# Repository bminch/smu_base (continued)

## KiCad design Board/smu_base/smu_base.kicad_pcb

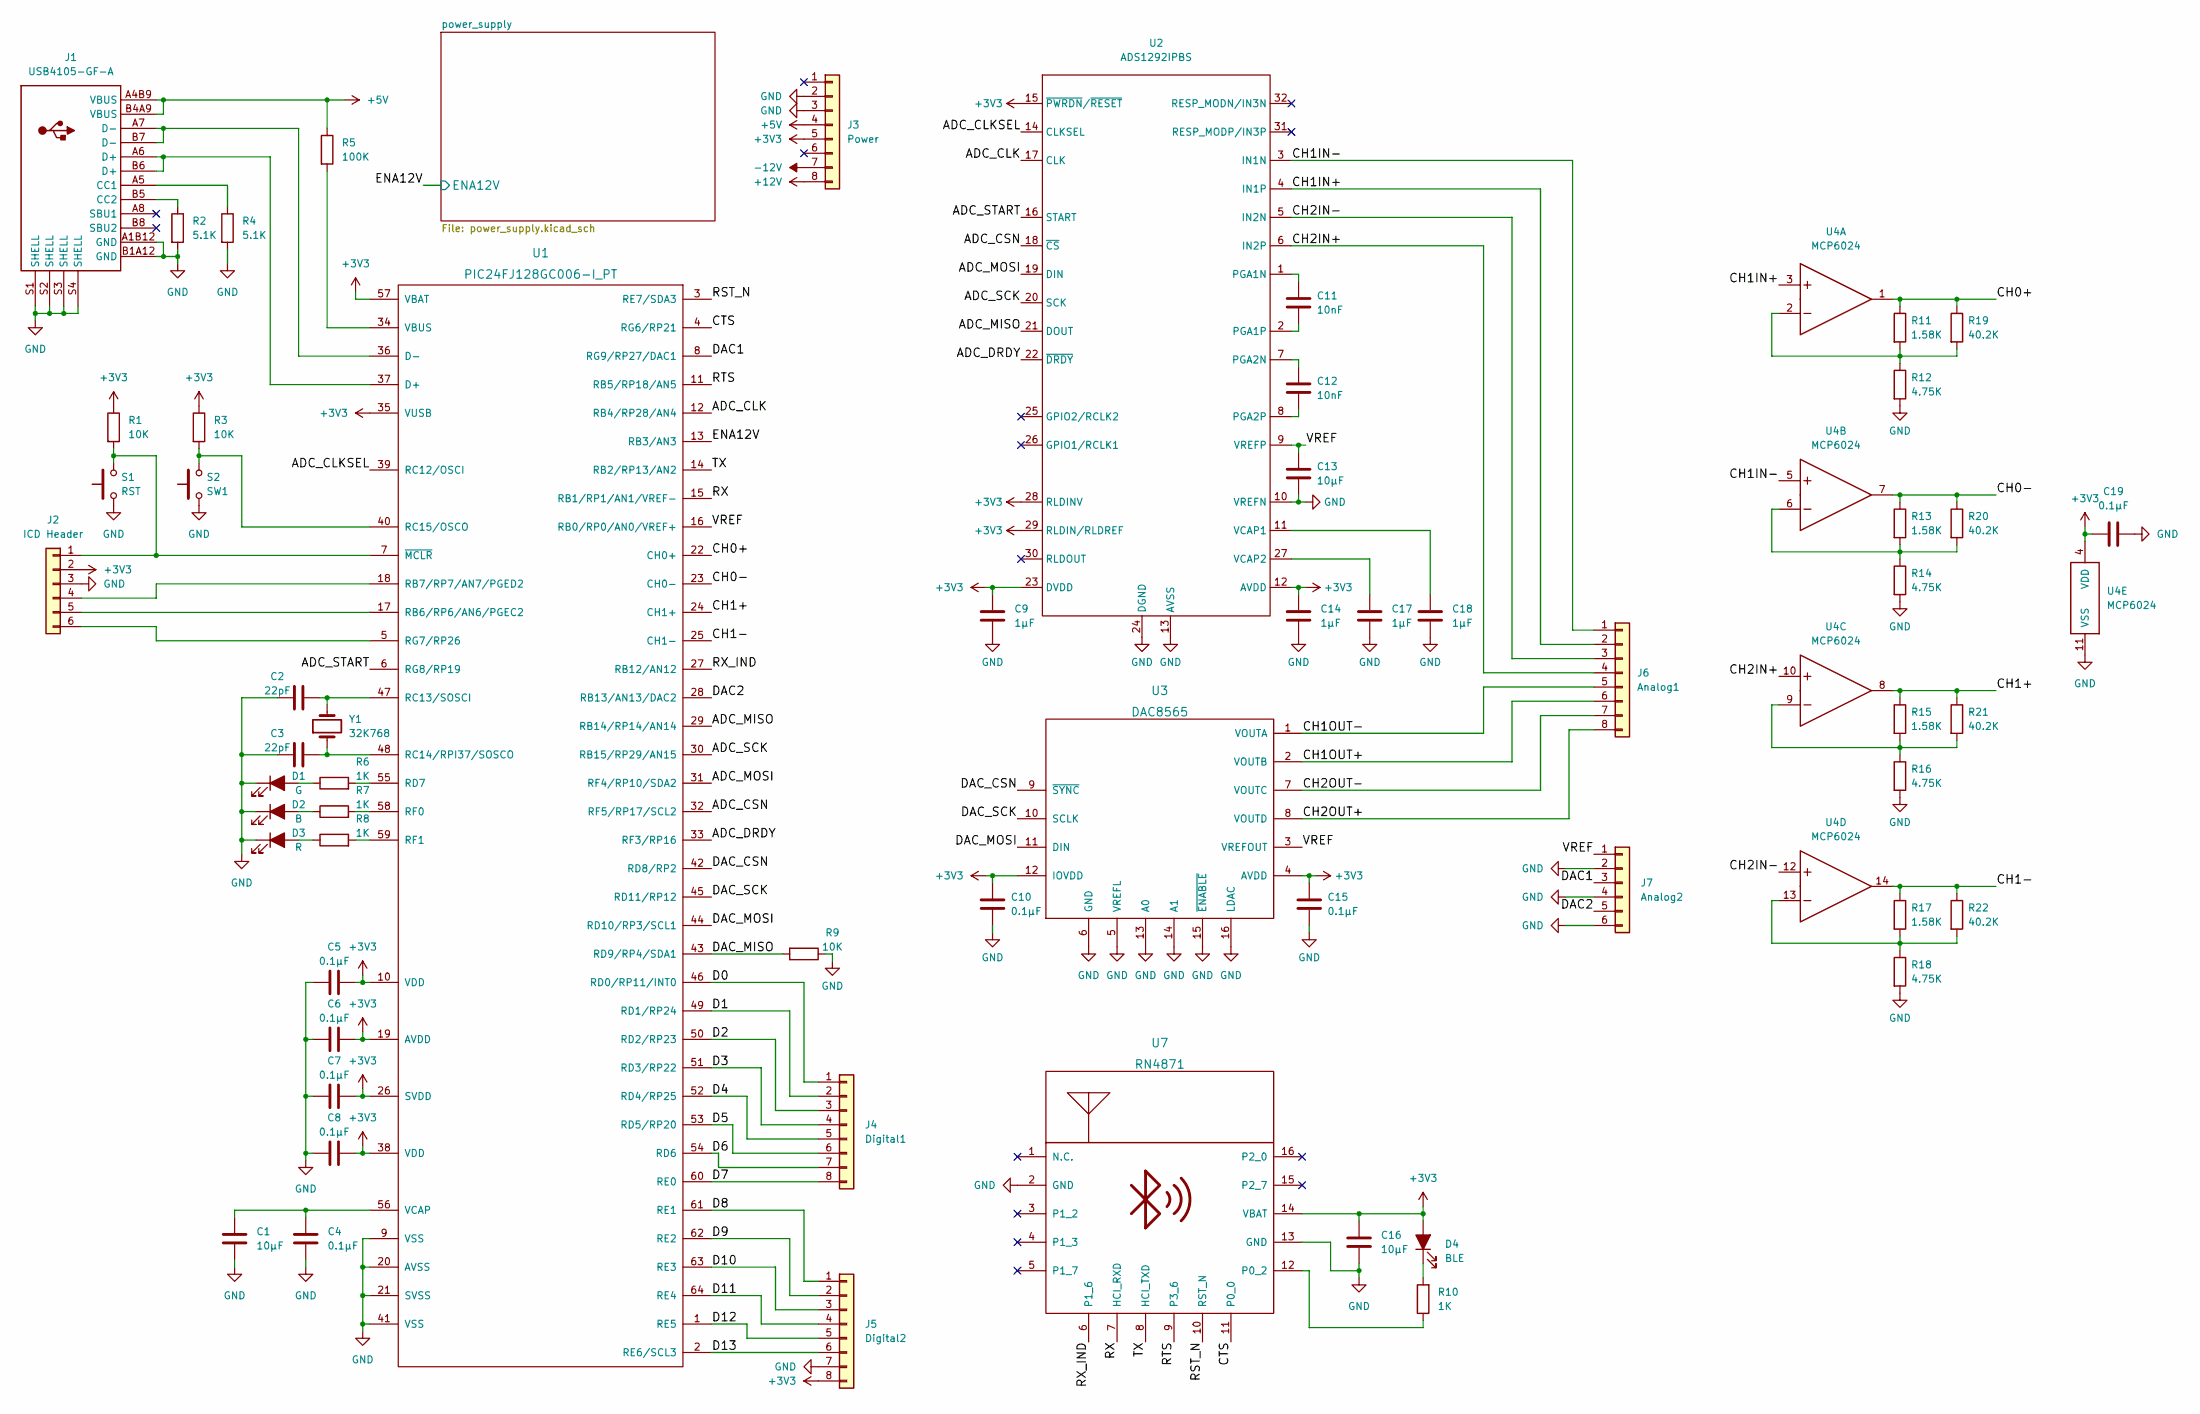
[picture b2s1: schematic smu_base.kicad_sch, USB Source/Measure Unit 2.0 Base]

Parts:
C1, C13, C16: 10µF; C_0603_1608Metric
C2, C3: 22pF; C_0603_1608Metric
C4, C5, C6, C7, C8, C10, C15, C19: 0.1µF; C_0603_1608Metric
C9, C14, C17, C18: 1µF; C_0603_1608Metric
C11, C12: 10nF; C_0603_1608Metric
D1: G; LED_0805_2012Metric
D2: B; LED_0805_2012Metric
D3: R; LED_0805_2012Metric
D4: BLE; LED_0805_2012Metric
J1: USB4105-GF-A
J2: ICD Header; ICD3_header
J3: Power; PinSocket_1x08_P2.54mm_Vertical
J4: Digital1; PinSocket_1x08_P2.54mm_Vertical
J5: Digital2; PinSocket_1x08_P2.54mm_Vertical
J6: Analog1; PinSocket_1x08_P2.54mm_Vertical
J7: Analog2; PinSocket_1x06_P2.54mm_Vertical
R1, R3, R9: 10K; R_0603_1608Metric
R2, R4: 5.1K; R_0603_1608Metric
R5: 100K; R_0603_1608Metric
R6, R7, R8, R10: 1K; R_0603_1608Metric
R11, R13, R15, R17: 1.58K; R_0603_1608Metric
R12, R14, R16, R18: 4.75K; R_0603_1608Metric
R19, R20, R21, R22: 40.2K; R_0603_1608Metric
S1: RST; TL3301NFxxxxJ
S2: SW1; TL3301AFxxxxJ
U1: PIC24FJ128GC006-I_PT; TQFP-64_10x10mm_P0.5mm
U2: ADS1292IPBS; PQFP-32_5x5mm_P0.5mm
U3: DAC8565; TSSOP-16_4.4x5mm_P0.65mm
U4: MCP6024; TSSOP-14_4.4x5mm_P0.65mm
U7: RN4871
Y1: 32K768; Crystal_SMD_2012-2Pin_2.0x1.2mm

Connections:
+3V3: C5.2, C6.2, C7.2, C8.2, C9.1, C10.1, C14.1, C15.1, C16.1, C19.1, D4.2 (A), J2.2, J3.5, J5.8, R1.1, R3.1, U1.10 (VDD), U1.19 (AVDD), U1.26 (SVDD), U1.35 (VUSB), U1.38 (VDD), U1.57 (VBAT), U2.12 (AVDD), U2.15 (~PWRDN/~RESET), U2.23 (DVDD), U2.28 (RLDINV), U2.29 (RLDIN/RLDREF), U3.4 (AVDD), U3.12 (IOVDD), U4.4 (VDD), U7.14 (VBAT); also elsewhere on the board
+5V: J1.A4B9 (VBUS), J1.B4A9 (VBUS), J3.4, R5.1; also elsewhere on the board
+12V: J3.8; also elsewhere on the board
-12V: J3.7; also elsewhere on the board
/ADC_CLK: U1.12 (RB4/RP28/AN4), U2.17 (CLK)
/ADC_CLKSEL: U1.39 (RC12/OSCI), U2.14 (CLKSEL)
/ADC_CSN: U1.32 (RF5/RP17/SCL2), U2.18 (~CS)
/ADC_DRDY: U1.33 (RF3/RP16), U2.22 (~DRDY)
/ADC_MISO: U1.29 (RB14/RP14/AN14), U2.21 (DOUT)
/ADC_MOSI: U1.31 (RF4/RP10/SDA2), U2.19 (DIN)
/ADC_SCK: U1.30 (RB15/RP29/AN15), U2.20 (SCK)
/ADC_START: U1.6 (RG8/RP19), U2.16 (START)
/CH0+: R11.1, R19.1, U1.22 (CH0+), U4.1
/CH0-: R13.1, R20.1, U1.23 (CH0-), U4.7
/CH1+: R15.1, R21.1, U1.24 (CH1+), U4.8
/CH1-: R17.1, R22.1, U1.25 (CH1-), U4.14
/CH1IN+: J6.2, U2.4 (IN1P), U4.3
/CH1IN-: J6.1, U2.3 (IN1N), U4.5
/CH1OUT+: J6.6, U3.2 (VOUTB)
/CH1OUT-: J6.5, U3.1 (VOUTA)
/CH2IN+: J6.4, U2.6 (IN2P), U4.10
/CH2IN-: J6.3, U2.5 (IN2N), U4.12
/CH2OUT+: J6.8, U3.8 (VOUTD)
/CH2OUT-: J6.7, U3.7 (VOUTC)
/CTS: U1.4 (RG6/RP21), U7.11 (P0_0)
/D0: J4.1, U1.46 (RD0/RP11/INT0)
/D1: J4.2, U1.49 (RD1/RP24)
/D2: J4.3, U1.50 (RD2/RP23)
/D3: J4.4, U1.51 (RD3/RP22)
/D4: J4.5, U1.52 (RD4/RP25)
/D5: J4.6, U1.53 (RD5/RP20)
/D6: J4.7, U1.54 (RD6)
/D7: J4.8, U1.60 (RE0)
/D8: J5.1, U1.61 (RE1)
/D9: J5.2, U1.62 (RE2)
/D10: J5.3, U1.63 (RE3)
/D11: J5.4, U1.64 (RE4)
/D12: J5.5, U1.1 (RE5)
/D13: J5.6, U1.2 (RE6/SCL3)
/DAC1: J7.3, U1.8 (RG9/RP27/DAC1)
/DAC2: J7.5, U1.28 (RB13/AN13/DAC2)
/DAC_CSN: U1.42 (RD8/RP2), U3.9 (~SYNC)
/DAC_MISO: R9.2, U1.43 (RD9/RP4/SDA1)
/DAC_MOSI: U1.44 (RD10/RP3/SCL1), U3.11 (DIN)
/DAC_SCK: U1.45 (RD11/RP12), U3.10 (SCLK)
/ENA12V: U1.13 (RB3/AN3); also elsewhere on the board
/RST_N: U1.3 (RE7/SDA3), U7.10 (RST_N)
/RTS: U1.11 (RB5/RP18/AN5), U7.9 (P3_6)
/RX: U1.15 (RB1/RP1/AN1/VREF-), U7.7 (HCI_RXD)
/RX_IND: U1.27 (RB12/AN12), U7.6 (P1_6)
/TX: U1.14 (RB2/RP13/AN2), U7.8 (HCI_TXD)
/VREF: C13.1, J7.1, U1.16 (RB0/RP0/AN0/VREF+), U2.9 (VREFP), U3.3 (VREFOUT)
GND: C1.2, C2.1, C3.1, C4.2, C5.1, C6.1, C7.1, C8.1, C9.2, C10.2, C13.2, C14.2, C15.2, C16.2, C17.2, C18.2, C19.2, D1.1 (K), D2.1 (K), D3.1 (K), J1.A1B12 (GND), J1.B1A12 (GND), J1.S1 (SHELL), J1.S2 (SHELL), J1.S3 (SHELL), J1.S4 (SHELL), J2.3, J3.2, J3.3, J5.7, J7.2, J7.4, J7.6, R2.2, R4.2, R9.1, R12.2, R14.2, R16.2, R18.2, S1.1, S2.1, U1.9 (VSS), U1.20 (AVSS), U1.21 (SVSS), U1.41 (VSS), U2.10 (VREFN), U2.13 (AVSS), U2.24 (DGND), U3.5 (VREFL), U3.6 (GND), U3.13 (A0), U3.14 (A1), U3.15 (~ENABLE), U3.16 (LDAC), U4.11 (VSS), U7.2 (GND), U7.13 (GND); also elsewhere on the board
unnamed: C1.1, C4.1, U1.56 (VCAP)
unnamed: C2.2, U1.47 (RC13/SOSCI), Y1.2
unnamed: C3.2, U1.48 (RC14/RPI37/SOSCO), Y1.1
unnamed: C11.1, U2.1 (PGA1N)
unnamed: C11.2, U2.2 (PGA1P)
unnamed: C12.1, U2.7 (PGA2N)
unnamed: C12.2, U2.8 (PGA2P)
unnamed: C17.1, U2.27 (VCAP2)
unnamed: C18.1, U2.11 (VCAP1)
unnamed: D1.2 (A), R6.1
unnamed: D2.2 (A), R7.1
unnamed: D3.2 (A), R8.1
unnamed: D4.1 (K), R10.2
unnamed: J1.A5 (CC1), R4.1
unnamed: J1.A6 (D+), J1.B6 (D+), U1.37 (D+)
unnamed: J1.A7 (D-), J1.B7 (D-), U1.36 (D-)
unnamed: J1.B5 (CC2), R2.1
unnamed: J2.1, R1.2, S1.2, U1.7 (~MCLR)
unnamed: J2.4, U1.18 (RB7/RP7/AN7/PGED2)
unnamed: J2.5, U1.17 (RB6/RP6/AN6/PGEC2)
unnamed: J2.6, U1.5 (RG7/RP26)
unnamed: R3.2, S2.2, U1.40 (RC15/OSCO)
unnamed: R5.2, U1.34 (VBUS)
unnamed: R6.2, U1.55 (RD7)
unnamed: R7.2, U1.58 (RF0)
unnamed: R8.2, U1.59 (RF1)
unnamed: R10.1, U7.12 (P0_2)
unnamed: R11.2, R12.1, R19.2, U4.2
unnamed: R13.2, R14.1, R20.2, U4.6
unnamed: R15.2, R16.1, R21.2, U4.9
unnamed: R17.2, R18.1, R22.2, U4.13

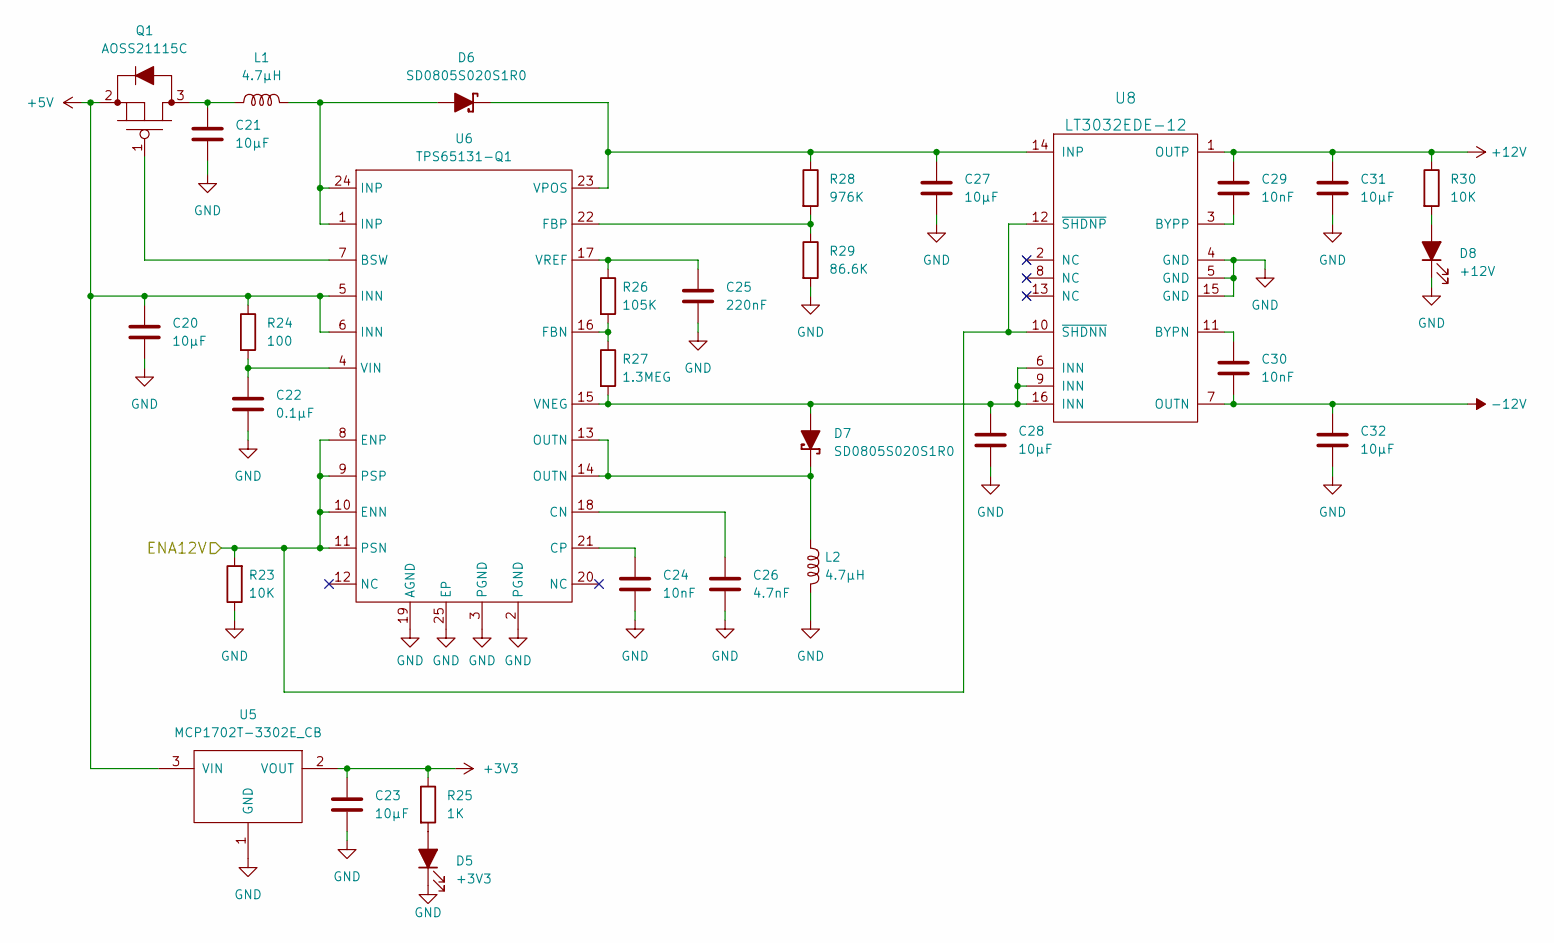
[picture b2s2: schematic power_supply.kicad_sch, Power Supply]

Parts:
C20, C21, C23, C27, C28, C31, C32: 10µF; C_0603_1608Metric
C22: 0.1µF; C_0603_1608Metric
C24, C29, C30: 10nF; C_0603_1608Metric
C25: 220nF; C_0603_1608Metric
C26: 4.7nF; C_0603_1608Metric
D5: +3V3; LED_0805_2012Metric
D6, D7: SD0805S020S1R0; D_0805_2012Metric
D8: +12V; LED_0805_2012Metric
L1, L2: 4.7µH; PA5003.182NLT
Q1: AOSS21115C; SOT-23
R23, R30: 10K; R_0603_1608Metric
R24: 100; R_0603_1608Metric
R25: 1K; R_0603_1608Metric
R26: 105K; R_0603_1608Metric
R27: 1.3MEG; R_0603_1608Metric
R28: 976K; R_0603_1608Metric
R29: 86.6K; R_0603_1608Metric
U5: MCP1702T-3302E_CB; SOT-23
U6: TPS65131-Q1; TPS65131-Q
U8: LT3032EDE-12; LT3032

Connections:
+3V3: C23.1, R25.1, U5.2 (VOUT); also elsewhere on the board
+5V: C20.1, Q1.2, R24.1, U5.3 (VIN), U6.5 (INN), U6.6 (INN); also elsewhere on the board
+12V: C29.1, C31.1, R30.1, U8.1 (OUTP); also elsewhere on the board
-12V: C30.2, C32.1, U8.7 (OUTN); also elsewhere on the board
/ENA12V: R23.2, U6.8 (ENP), U6.9 (PSP), U6.10 (ENN), U6.11 (PSN), U8.10 (~SHDNN), U8.12 (~SHDNP); also elsewhere on the board
GND: C20.2, C21.2, C22.2, C23.2, C24.2, C25.2, C26.2, C27.2, C28.2, C31.2, C32.2, D5.1 (K), D8.1 (K), L2.2, R23.1, R29.2, U5.1 (GND), U6.2 (PGND), U6.3 (PGND), U6.19 (AGND), U6.25 (EP), U8.4 (GND), U8.5 (GND), U8.15 (GND); also elsewhere on the board
unnamed: C21.1, L1.1, Q1.3
unnamed: C22.1, R24.2, U6.4 (VIN)
unnamed: C24.1, U6.21 (CP)
unnamed: C25.1, R26.1, U6.17 (VREF)
unnamed: C26.1, U6.18 (CN)
unnamed: C27.1, D6.1, R28.1, U6.23 (VPOS), U8.14 (INP)
unnamed: C28.1, D7.2, R27.2, U6.15 (VNEG), U8.6 (INN), U8.9 (INN), U8.16 (INN)
unnamed: C29.2, U8.3 (BYPP)
unnamed: C30.1, U8.11 (BYPN)
unnamed: D5.2 (A), R25.2
unnamed: D6.2, L1.2, U6.1 (INP), U6.24 (INP)
unnamed: D7.1, L2.1, U6.13 (OUTN), U6.14 (OUTN)
unnamed: D8.2 (A), R30.2
unnamed: Q1.1, U6.7 (BSW)
unnamed: R26.2, R27.1, U6.16 (FBN)
unnamed: R28.2, R29.1, U6.22 (FBP)

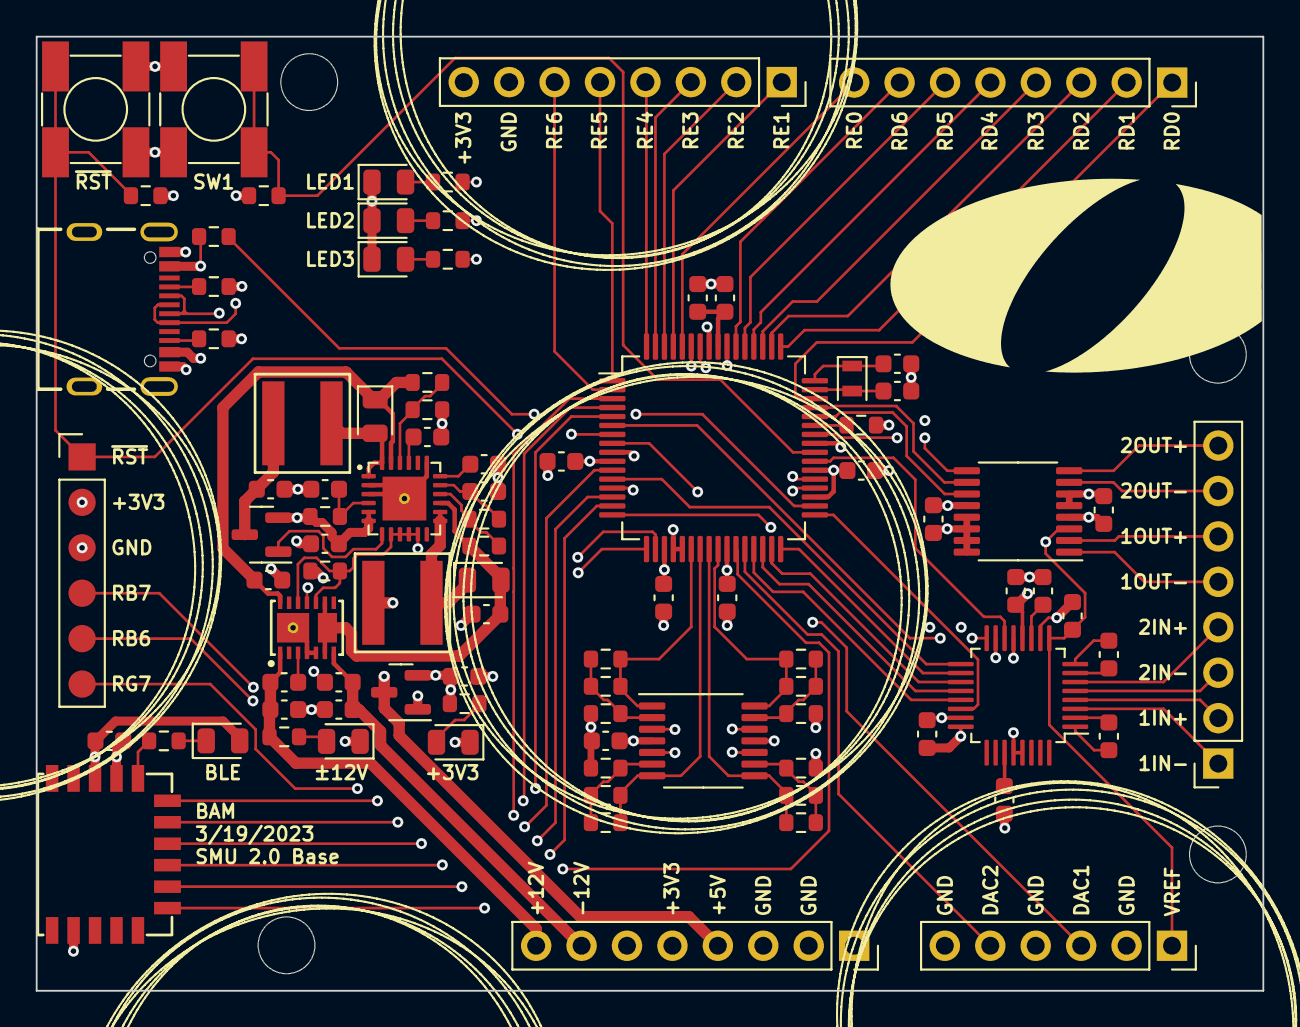
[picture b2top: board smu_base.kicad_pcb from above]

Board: 4 copper layers, 68.6 x 53.3 mm, 98 parts (1 on the bottom side), 100 nets.

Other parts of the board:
svg2mod, svg2mod#2, svg2mod#3, svg2mod#4, svg2mod#6: G***; gesture_ellipse
svg2mod#5: G***; OlinLogoTruncated_0.4in
svg2mod#7: G***; OlinLogoTruncatedLg

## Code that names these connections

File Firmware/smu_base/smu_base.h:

#ifndef _SMUBASE_H_
#define _SMUBASE_H_

#include "pic24fj.h"
#include "common.h"
#include <stdint.h>

// LED pin definitions
#define LED1                LATDbits.LATD7
#define LED2                LATFbits.LATF0
#define LED3                LATFbits.LATF1

#define LED1_DIR            TRISDbits.TRISD7
#define LED2_DIR            TRISFbits.TRISF0
#define LED3_DIR            TRISFbits.TRISF1

// Tactile switch pin definitions
#define SW1                 PORTCbits.RC15
#define SW1_DIR             TRISCbits.TRISC15

// Power supply pin definitions
#define ENA12V              LATBbits.LATB3
#define ENA12V_DIR          TRISBbits.TRISB3

// Digital header pin definitions
#define RD0_                LATDbits.LATD0
#define RD1_                LATDbits.LATD1
#define RD2_                LATDbits.LATD2
#define RD3_                LATDbits.LATD3
#define RD4_                LATDbits.LATD4
#define RD5_                LATDbits.LATD5
#define RD6_                LATDbits.LATD6
#define RE0_                LATEbits.LATE0
#define RE1_                LATEbits.LATE1
#define RE2_                LATEbits.LATE2
#define RE3_                LATEbits.LATE3
#define RE4_                LATEbits.LATE4
#define RE5_                LATEbits.LATE5
#define RE6_                LATEbits.LATE6

#define RD0_DIR             TRISDbits.TRISD0
#define RD1_DIR             TRISDbits.TRISD1
#define RD2_DIR             TRISDbits.TRISD2
#define RD3_DIR             TRISDbits.TRISD3
#define RD4_DIR             TRISDbits.TRISD4
#define RD5_DIR             TRISDbits.TRISD5
#define RD6_DIR             TRISDbits.TRISD6
#define RE0_DIR             TRISEbits.TRISE0
#define RE1_DIR             TRISEbits.TRISE1
#define RE2_DIR             TRISEbits.TRISE2
#define RE3_DIR             TRISEbits.TRISE3
#define RE4_DIR             TRISEbits.TRISE4
#define RE5_DIR             TRISEbits.TRISE5
#define RE6_DIR             TRISEbits.TRISE6

// DAC16 (DAC8565) pin definitions
#define DAC_CSN             LATDbits.LATD8
#define DAC_SCK             LATDbits.LATD11
#define DAC_MOSI            LATDbits.LATD10
#define DAC_MISO            PORTDbits.RD9

#define DAC_CSN_DIR         TRISDbits.TRISD8
#define DAC_SCK_DIR         TRISDbits.TRISD11
#define DAC_MOSI_DIR        TRISDbits.TRISD10
#define DAC_MISO_DIR        TRISDbits.TRISD9

#define DAC_CSN_RP          2
#define DAC_SCK_RP          12
#define DAC_MOSI_RP         3
#define DAC_MISO_RP         4

// ADC24 (ADS1292) pin definitions
#define ADC_CSN             LATFbits.LATF5
#define ADC_SCK             LATBbits.LATB15
#define ADC_MOSI            LATFbits.LATF4
#define ADC_MISO            PORTBbits.RB14
#define ADC_START           LATGbits.LATG8
#define ADC_DRDY            PORTFbits.RF3
#define ADC_CLKSEL          LATCbits.LATC12
#define ADC_CLK             LATBbits.LATB4

#define ADC_CSN_DIR         TRISFbits.TRISF5
#define ADC_SCK_DIR         TRISBbits.TRISB15
#define ADC_MOSI_DIR        TRISFbits.TRISF4
#define ADC_MISO_DIR        TRISBbits.TRISB14
#define ADC_START_DIR       TRISGbits.TRISG8
#define ADC_DRDY_DIR        TRISFbits.TRISF3
#define ADC_CLKSEL_DIR      TRISCbits.TRISC12
#define ADC_CLK_DIR         TRISBbits.TRISB4

#define ADC_CSN_RP          17
#define ADC_SCK_RP          29
#define ADC_MOSI_RP         10
#define ADC_MISO_RP         14
#define ADC_START_RP        19
#define ADC_DRDY_RP         16
#define ADC_CLK_RP          28

// BLE module (RN4871) pin definitions
#define BLE_RX_IND          LATBbits.LATB12
#define BLE_RST_N           LATEbits.LATE7
#define BLE_RX              PORTBbits.RB1
#define BLE_TX              PORTBbits.RB2
#define BLE_RTS             PORTBbits.RB5
#define BLE_CTS             PORTGbits.RG6

#define BLE_RX_IND_DIR      TRISBbits.TRISB12
#define BLE_RST_N_DIR       TRISEbits.TRISE7
#define BLE_RX_DIR          TRISBbits.TRISB1
#define BLE_TX_DIR          TRISBbits.TRISB2
#define BLE_RTS_DIR         TRISBbits.TRISB5
#define BLE_CTS_DIR         TRISGbits.TRISG6

#define BLE_RX_RP           1
#define BLE_TX_RP           13
#define BLE_RTS_RP          18
#define BLE_CTS_RP          21

// Peripheral remappable pin definitions
#define INT1_RP             1
#define INT2_RP             2
#define INT3_RP             3
#define INT4_RP             4

#define MOSI1_RP            7
#define SCK1OUT_RP          8
#define MOSI2_RP            10
#define SCK2OUT_RP          11

#define MISO1_RP            40
#define SCK1IN_RP           41
#define MISO2_RP            44
#define SCK2IN_RP           45

#define OC1_RP              18
#define OC2_RP              19
#define OC3_RP              20
#define OC4_RP              21
#define OC5_RP              22
#define OC6_RP              23
#define OC7_RP              24
#define OC8_RP              25
#define OC9_RP              35

#define U1TX_RP             3
#define U1RTS_RP            4
#define U2TX_RP             5
#define U2RTS_RP            6
#define U3TX_RP             28
#define U3RTS_RP            29
#define U4TX_RP             30
#define U4RTS_RP            31

#define U1RX_RP             36
#define U1CTS_RP            37
#define U2RX_RP             38
#define U2CTS_RP            39
#define U3RX_RP             35
#define U3CTS_RP            43
#define U4RX_RP             54
#define U4CTS_RP            55

// Convenience boolean values definitions
#define FALSE               0
#define TRUE                1

#define OFF                 0
#define ON                  1

#define OUT                 0
#define IN                  1

// ADS1292 SPI commands
#define ADC24_CMD_WAKEUP    0x02
#define ADC24_CMD_STANDBY   0x04
#define ADC24_CMD_RESET     0x06
#define ADC24_CMD_START     0x08
#define ADC24_CMD_STOP      0x0A
#define ADC24_CMD_OFFSETCAL 0x1A
#define ADC24_CMD_RDATAC    0x10
#define ADC24_CMD_SDATAC    0x11
#define ADC24_CMD_RDATA     0x12
#define ADC24_CMD_RREG      0x20
#define ADC24_CMD_WREG      0x40

// ADS1292 register definitions
#define ADC24_REG_ID        0x00
#define ADC24_REG_CONFIG1   0x01
#define ADC24_REG_CONFIG2   0x02
#define ADC24_REG_LOFF      0x03
#define ADC24_REG_CH1SET    0x04
#define ADC24_REG_CH2SET    0x05
#define ADC24_REG_RLD_SENS  0x06
#define ADC24_REG_LOFF_SENS 0x07
#define ADC24_REG_LOFF_STAT 0x08
#define ADC24_REG_RESP1     0x09
#define ADC24_REG_RESP2     0x0A
#define ADC24_REG_GPIO      0x0B

#define U1TX_BUFFER_LENGTH  1024
#define U1RX_BUFFER_LENGTH  1024

typedef struct {
    uint8_t *data;
    uint16_t length;
    uint16_t head;
    uint16_t tail;
    uint16_t count;
} RINGBUFFER;

extern RINGBUFFER U1TXbuffer, U1RXbuffer;
extern uint8_t U1TX_buffer[];
extern uint8_t U1RX_buffer[];
extern uint16_t U1TXthreshold;

void init_smu_base(void);

void init_adc16(void);
void adc16_calibrate(void);
int16_t adc16_meas_ch1_raw(void);
int16_t adc16_meas_ch2_raw(void);
int16_t adc16_meas_ch1(void);
int16_t adc16_meas_ch2(void);
int16_t adc16_meas_ch1_avg(void);
int16_t adc16_meas_ch2_avg(void);
int16_t adc16_get_offset(void);
uint16_t adc16_get_max_val(void);

void init_dac16(void);
uint16_t dac16_get_dac0(void);
void dac16_set_dac0(uint16_t val);
uint16_t dac16_get_dac1(void);
void dac16_set_dac1(uint16_t val);
uint16_t dac16_get_dac2(void);
void dac16_set_dac2(uint16_t val);
uint16_t dac16_get_dac3(void);
void dac16_set_dac3(uint16_t val);
void dac16_set_ch1(uint16_t pos, uint16_t neg);
void dac16_set_ch2(uint16_t pos, uint16_t neg);

void init_adc24(void);
void adc24_calibrate(void);
void adc24_command(uint8_t cmd);
void adc24_write_reg(uint8_t reg, uint8_t val);
uint8_t adc24_read_reg(uint8_t reg);
void adc24_read_data(int32_t *ch1val, int32_t *ch2val);
void adc24_meas_both(int32_t *ch1val, int32_t *ch2val);
void adc24_meas_both_avg(int32_t *ch1val, int32_t *ch2val);
void adc24_meas_both_raw(int32_t *ch1val, int32_t *ch2val);
void adc24_set_ch1offset(int32_t val);
int32_t adc24_get_ch1offset(void);
void adc24_set_ch2offset(int32_t val);
int32_t adc24_get_ch2offset(void);

void init_ble(void);
uint16_t ble_in_waiting(void);
void ble_putc(uint8_t ch);
uint8_t ble_getc(void);
void ble_puts(uint8_t *str);

uint16_t dummy_in_waiting(void);
void dummy_putc(uint8_t ch);
uint8_t dummy_getc(void);
void dummy_puts(uint8_t *str);

uint16_t U1inWaiting(void);
void U1flushTxBuffer(void);
void U1putc(uint8_t ch);
uint8_t U1getc(void);
void U1puts(uint8_t *str);
void U1gets(uint8_t *str, uint16_t len);
void U1gets_term(uint8_t *str, uint16_t len);

#endif

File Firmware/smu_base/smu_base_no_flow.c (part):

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    ANSF = 0;
    ANSG = 0;

    ANSBbits.ANSB0 = 1;     // configure RB0 (AN0) for analog function
    TRISBbits.TRISB0 = 1;   // tristate RB0's output driver

    ANSGbits.ANSG9 = 1;     // configure RG9 (DAC1) for analog function
    TRISGbits.TRISG9 = 1;   // tristate RG9's output driver
    DAC1CON = 0x8081;       // enable DAC1, no trigger, and reference is DREF+
    DAC1DAT = 0;

    ANSBbits.ANSB13 = 1;    // configure RB13 (DAC2) for analog function
    TRISBbits.TRISB13 = 1;  // tristate RB13's output driver
    DAC2CON = 0x8081;       // enable DAC2, no trigger, and reference is DREF+
    DAC2DAT = 0;

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    // Configure SW pin as inputs
    SW1_DIR = IN;

    // Configure ENA12V pin as an output, set to low (off)
    ENA12V = OFF; ENA12V_DIR = OUT;

    // Configure digital header pins as outputs, set to low
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    uint8_t *RPOR, *RPINR;

    // Configure DAC16 pins and SPI peripheral (SPI1)
    DAC_CSN_DIR = OUT; DAC_CSN = 1;
    DAC_SCK_DIR = OUT; DAC_SCK = 1;
    DAC_MOSI_DIR = OUT; DAC_MOSI = 0;
    DAC_MISO_DIR = IN;

    RPOR = (uint8_t *)&RPOR0;
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
    dac16_dac0 = val;

    DAC_CSN = 0;

    // Write to buffer with data and load DAC0
    SPI1BUF = 0b00010000;
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    while (SPI1STATbits.SPIRBF == 0) {}
    temp = SPI1BUF;

    DAC_CSN = 1;
}

uint16_t dac16_get_dac1(void) {
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
    dac16_dac1 = val;

    DAC_CSN = 0;

    // Write to buffer with data and load DAC1
    SPI1BUF = 0b00010010;
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    while (SPI1STATbits.SPIRBF == 0) {}
    temp = SPI1BUF;

    DAC_CSN = 1;
}

uint16_t dac16_get_dac2(void) {
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
    dac16_dac2 = val;

    DAC_CSN = 0;

    // Write to buffer with data and load DAC2
    SPI1BUF = 0b00010100;
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    while (SPI1STATbits.SPIRBF == 0) {}
    temp = SPI1BUF;

    DAC_CSN = 1;
}

uint16_t dac16_get_dac3(void) {
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
    dac16_dac3 = val;

    DAC_CSN = 0;

    // Write to buffer with data and load DAC3
    SPI1BUF = 0b00010110;
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    while (SPI1STATbits.SPIRBF == 0) {}
    temp = SPI1BUF;

    DAC_CSN = 1;
}

void dac16_set_ch1(uint16_t pos, uint16_t neg) {
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
    dac16_dac0 = neg;

    DAC_CSN = 0;

    // Write to buffer 0 with data
    SPI1BUF = 0b00000000;
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    while (SPI1STATbits.SPIRBF == 0) {}
    temp = SPI1BUF;

    DAC_CSN = 1;

    dac16_dac1 = pos;

    DAC_CSN = 0;

    // Write to buffer 1 with data and load all DACs simultaneously
    SPI1BUF = 0b00100010;
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    while (SPI1STATbits.SPIRBF == 0) {}
    temp = SPI1BUF;

    DAC_CSN = 1;
}

void dac16_set_ch2(uint16_t pos, uint16_t neg) {
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
    dac16_dac2 = neg;

    DAC_CSN = 0;

    // Write to buffer 2 with data
    SPI1BUF = 0b00000100;
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    while (SPI1STATbits.SPIRBF == 0) {}
    temp = SPI1BUF;

    DAC_CSN = 1;

    dac16_dac3 = pos;

    DAC_CSN = 0;

    // Write to buffer 3 with data and load all DACs simultaneously
    SPI1BUF = 0b00100110;
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    while (SPI1STATbits.SPIRBF == 0) {}
    temp = SPI1BUF;

    DAC_CSN = 1;
}

// Functions for interfacing with the 2-channel, 24-bit sigma-delta ADC (ADS1292)
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    uint16_t i;

    // Configure ADC24 pins, SPI peripheral (SPI2), and clock (OC1)
    ADC_CSN_DIR = OUT; ADC_CSN = 1;
    ADC_SCK_DIR = OUT; ADC_SCK = 0;
    ADC_MOSI_DIR = OUT; ADC_MOSI = 0;
    ADC_MISO_DIR = IN;
    ADC_START_DIR = OUT; ADC_START = 0;
    ADC_DRDY_DIR = IN;
    ADC_CLKSEL_DIR = OUT; ADC_CLKSEL = 0;
    ADC_CLK_DIR = OUT; ADC_CLK = 0;

    RPOR = (uint8_t *)&RPOR0;
    RPINR = (uint8_t *)&RPINR0;
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    adc24_ch1offset = 0;
    adc24_ch2offset = 0;

    ADC_START = 1;

    while (ADC_DRDY == 1) {}
    adc24_read_data(&ch1val, &ch2val);
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        adc24_ch2offset += ch2val;
    }

    ADC_START = 0;

    adc24_ch1offset = adc24_ch1offset / 9;
    adc24_ch2offset = adc24_ch2offset / 9;
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void adc24_command(uint8_t cmd) {
    uint16_t temp, i;

    ADC_CSN = 0;

    SPI2BUF = (uint16_t)cmd;
    while (SPI2STATbits.SPIRBF == 0) {}
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    // Delay for 4 clock periods (7.25 µs) before raising CSN
    for (i = 22; i; i--) {}

    ADC_CSN = 1;

    // Delay for 3 clock periods (5.5 µs) to meet minimum CSN high time
    for (i = 16; i; i--) {}
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void adc24_write_reg(uint8_t reg, uint8_t val) {
    uint16_t temp, i;

    ADC_CSN = 0;

    SPI2BUF = (uint16_t)(ADC24_CMD_WREG | reg);
    while (SPI2STATbits.SPIRBF == 0) {}
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    // Delay for 4 clock periods (7.25 µs) before raising CSN
    for (i = 22; i; i--) {}

    ADC_CSN = 1;

    // Delay for 3 clock periods (5.5 µs) to meet minimum CSN high time
    for (i = 16; i; i--) {}
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uint8_t adc24_read_reg(uint8_t reg) {
    uint16_t temp, i;

    ADC_CSN = 0;

    SPI2BUF = (uint16_t)(ADC24_CMD_RREG | reg);
    while (SPI2STATbits.SPIRBF == 0) {}
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    // Delay for 4 clock periods (7.25 µs) before raising CSN
    for (i = 22; i; i--) {}

    ADC_CSN = 1;

    // Delay for 3 clock periods (5.5 µs) to meet minimum CSN high time
    for (i = 16; i; i--) {}
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    uint16_t temp, i;
    int32_t val1, val2;

    ADC_CSN = 0;

    // Send the RDATA command
    SPI2BUF = (uint16_t)ADC24_CMD_RDATA;
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    // Delay for 4 clock periods (7.25 µs) before raising CSN
    for (i = 22; i; i--) {}

    ADC_CSN = 1;

    // Delay for 3 clock periods (5.5 µs) to meet minimum CSN high time
    for (i = 16; i; i--) {}
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void adc24_meas_both(int32_t *ch1val, int32_t *ch2val) {
    int32_t val1, val2;

    ADC_START = 1;

    while (ADC_DRDY == 1) {}
    adc24_read_data(&val1, &val2);
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    while (ADC_DRDY == 1) {}
    adc24_read_data(&val1, &val2);

    ADC_START = 0;

    *ch1val = val1 - adc24_ch1offset;
    *ch2val = val2 - adc24_ch2offset;
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    *ch1val = 0;
    *ch2val = 0;

    ADC_START = 1;

    while (ADC_DRDY == 1) {}
    adc24_read_data(&val1, &val2);
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        *ch2val += val2;
    }

    ADC_START = 0;

    *ch1val = (*ch1val / 9) - adc24_ch1offset;
    *ch2val = (*ch2val / 9) - adc24_ch2offset;
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void adc24_meas_both_raw(int32_t *ch1val, int32_t *ch2val) {
    int32_t val1, val2;

    ADC_START = 1;

    while (ADC_DRDY == 1) {}
    adc24_read_data(&val1, &val2);
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    while (ADC_DRDY == 1) {}
    adc24_read_data(&val1, &val2);

    ADC_START = 0;

    *ch1val = val1;
    *ch2val = val2;
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
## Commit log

2023-06-12 Initial commit.
2023-06-12 Add more files via upload.
2023-06-12 Add files via upload.
2023-06-12 Added via upload.
2023-06-13 Kicad Analog Shield Schematic Progress
2023-06-15 Analog front end schematic finished draft
2023-06-21 Analog Shield Layout Draft
2023-06-21 Adding B.Cu as a GND plane
2023-06-22 Correcting Trace Errors in Layout Draft
2023-06-22 Fixed Vias and Silkscreen References
